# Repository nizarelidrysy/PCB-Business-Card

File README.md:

# Nizar's PCB Business Card

This repository contains an open hardware business card running open source
software.

## Getting started

### Hardware

Using KiCad, add Silkscreen details such as your name. E.g. I added my contact
details and word cloud of my skills on the back of the PCB. Using the PCB Way
fabrication plugin of KiCAD, you can export the production files to directly
order the PCBs.

Note that when using vanilla PCB options (1.6 mm PCB thickness, HASL surface
finish) the USB connector will be a tad too thin to perfectly make contact with
a USB socket. Ideally you would use 2.0 mm PCB thickness and ENIG surface
finish, but that would be so expensive that it defeats the purpose of a
business card. Instead, you can just add a bit of solder on the USB contacts to
increase the thickness.

### Software

A simple "hello world" demo is given in
`software/RIOT-based-apps/apps/hello-world` that you can flash using e.g. a
J-Link EDU Mini programmer. Rather than using a cable, just plug the pins of
the J-Link EDU Mini programmer from the underside through the holes and rotate
the programmer until the pins and holes have contact. In addition, you need to
power the board (ideally via a USB-A extension cord).

With the programmer connected and the board powered, simply run:

    make flash

The "default" application will be `software/RIOT-based-apps/apps/games`, as
this contains a game launcher that allows running all currently added games.

Refer to the [RIOT documentation](https://doc.riot-os.org/) for more details on
the software.

---

<div align="center">
  <p>Engineered with dedication by Nizar EL IDRYSY ❤️</p>
</div>

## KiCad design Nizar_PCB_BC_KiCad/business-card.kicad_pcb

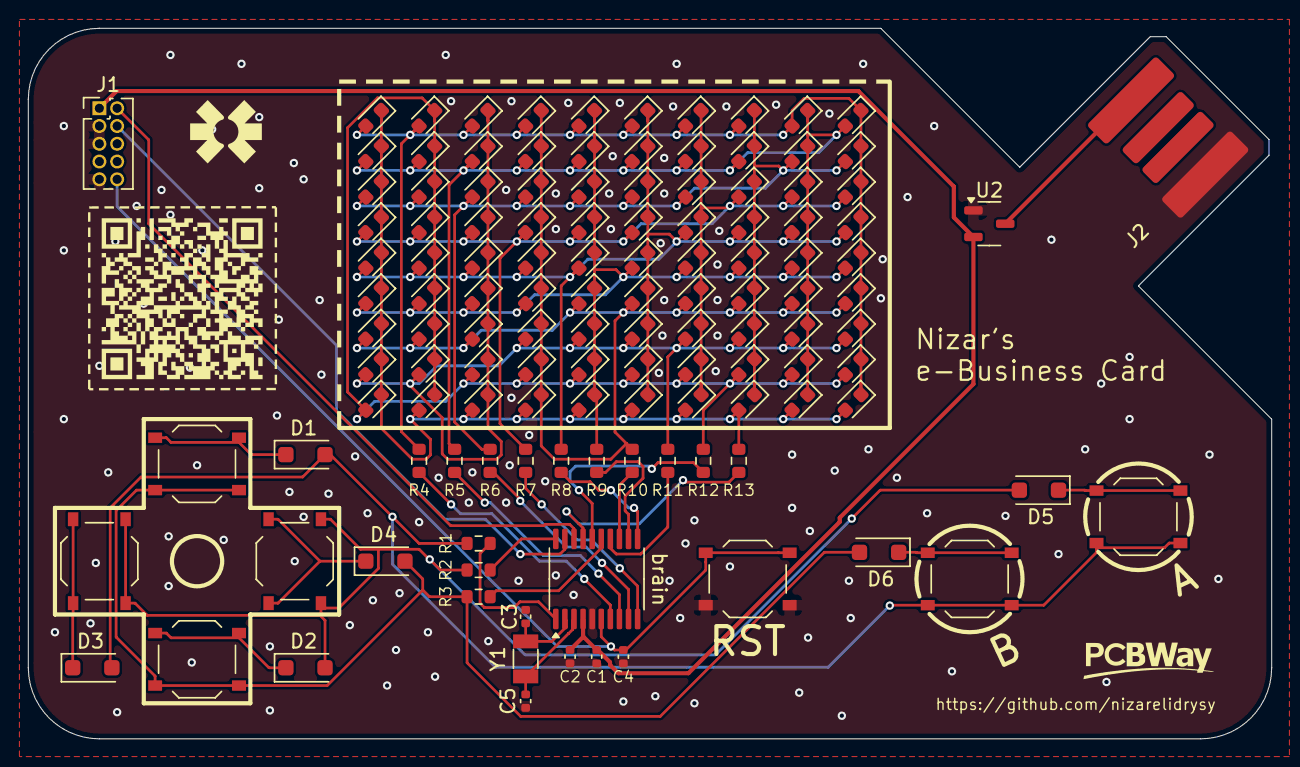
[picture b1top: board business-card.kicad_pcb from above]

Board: 2 copper layers, 88.9 x 50.8 mm, 126 parts (0 on the bottom side), 40 nets.

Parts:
C1, C4: 100 nF; C_0402_1005Metric
C2: 4.7 uF; C_0402_1005Metric
C3, C5: 10 pF; C_0402_1005Metric
D1, D2, D3, D4, D5, D6: D; D_SOD-123F
D7, D8, D9, D10, D11, D12, D13, D14, D15, D16, D17, D18, D19, D20, D21, D22, D23, D24, D25, D26, D27, D28, D29, D30, D31, D32, D33, D34, D35, D36, D37, D38, D39, D40, D41, D42, D43, D44, D45, D46, D47, D48, D49, D50, D51, D52, D53, D54, D55, D56, D57, D58, D59, D60, D61, D62, D63, D64, D65, D66, D67, D68, D69, D70, D71, D72, D73, D74, D75, D76, D77, D78, D79, D80, D81, D82, D83, D84, D85, D86, D87, D88, D89, D90, D91, D92, D93, D94, D95, D96: LED; LED_0603_1608Metric
J1: SWD; PinHeader_2x05_P1.27mm_Vertical
J2: USB_A_PCB_Edge_receptacle
R1, R2, R3, R4, R5, R6, R7, R8, R9, R10, R11, R12, R13: 75R; R_0603_1608Metric
SW1: BTN_UP; SW_Push_1P1T_XKB_TS-1187A
SW2: BTN_DOWN; SW_Push_1P1T_XKB_TS-1187A
SW3: BTN_LEFT; SW_Push_1P1T_XKB_TS-1187A
SW4: BTN_RIGHT; SW_Push_1P1T_XKB_TS-1187A
SW5: RST; SW_Push_1P1T_XKB_TS-1187A
SW6: BTN_A; SW_Push_1P1T_XKB_TS-1187A
SW7: BTN_B; SW_Push_1P1T_XKB_TS-1187A
U2: XC6206P332MR-G; SOT-23-3
Y1: 32.678 kHz; Crystal_SMD_3215-2Pin_3.2x1.5mm
brain: STM32G030F6Px; TSSOP-20_4.4x6.5mm_P0.65mm

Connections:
+5V: J2.1 (VBUS), U2.3 (VI)
/BM1: R1.1, brain.1 (PB7/PB8)
/BM2: R2.1, brain.20 (PB3/PB4/PB5/PB6)
/BM3: R3.1, brain.15 (PB0/PB1/PB2/PA8)
/NRST: C4.1, J1.10 (~RESET), SW5.1, brain.6 (NRST)
/OSC32_N: C3.1, Y1.1, brain.2 (PC14/PB9)
/OSC32_P: C5.1, Y1.2, brain.3 (PC15)
/PA0: R4.1, brain.7 (PA0)
/PA1: R5.1, brain.8 (PA1)
/PA2: R6.1, brain.9 (PA2)
/PA3: R7.1, brain.10 (PA3)
/PA4: R8.1, brain.11 (PA4)
/PA5: R9.1, brain.12 (PA5)
/PA6: R10.1, brain.13 (PA6)
/PA7: R11.1, brain.14 (PA7)
/PA9: R12.1, brain.16 (PA11/PA9)
/PA10: R13.1, brain.17 (PA12/PA10)
/SWCLK: J1.4 (SWCLK/TCK), brain.19 (PA14/PA15)
/SWDIO: J1.2 (SWDIO/TMS), brain.18 (PA13)
GND: C1.2, C2.2, C3.2, C4.2, C5.2, J1.3 (GND), J1.5 (GND), J1.9 (GNDDetect), J2.4 (GND), SW5.2, U2.1 (GND), brain.5 (VSS)
unnamed: D1.2 (A), D3.2 (A), R1.2, SW6.2, SW7.2
unnamed: D1.1 (K), SW1.1
unnamed: D2.2 (A), D5.2 (A), R2.2, SW3.2, SW4.2
unnamed: D2.1 (K), SW2.1
unnamed: D3.1 (K), SW3.1
unnamed: D4.2 (A), D6.2 (A), R3.2, SW1.2, SW2.2
unnamed: D4.1 (K), SW4.1
unnamed: D5.1 (K), SW6.1
unnamed: D6.1 (K), SW7.1
unnamed: D10.2 (A), D19.2 (A), D28.2 (A), D37.2 (A), D46.2 (A), D55.2 (A), D61.1 (K), D62.1 (K), D63.1 (K), D64.1 (K), D65.1 (K), D66.1 (K), D67.1 (K), D68.1 (K), D69.1 (K), D72.2 (A), D81.2 (A), D90.2 (A), R7.2
unnamed: D7.1 (K), D8.1 (K), D9.1 (K), D10.1 (K), D11.1 (K), D12.1 (K), D13.1 (K), D14.1 (K), D15.1 (K), D24.2 (A), D33.2 (A), D42.2 (A), D51.2 (A), D60.2 (A), D69.2 (A), D78.2 (A), D87.2 (A), D96.2 (A), R13.2
unnamed: D11.2 (A), D20.2 (A), D29.2 (A), D38.2 (A), D47.2 (A), D52.1 (K), D53.1 (K), D54.1 (K), D55.1 (K), D56.1 (K), D57.1 (K), D58.1 (K), D59.1 (K), D60.1 (K), D64.2 (A), D73.2 (A), D82.2 (A), D91.2 (A), R8.2
unnamed: D12.2 (A), D21.2 (A), D30.2 (A), D39.2 (A), D43.1 (K), D44.1 (K), D45.1 (K), D46.1 (K), D47.1 (K), D48.1 (K), D49.1 (K), D50.1 (K), D51.1 (K), D56.2 (A), D65.2 (A), D74.2 (A), D83.2 (A), D92.2 (A), R9.2
unnamed: D13.2 (A), D22.2 (A), D31.2 (A), D34.1 (K), D35.1 (K), D36.1 (K), D37.1 (K), D38.1 (K), D39.1 (K), D40.1 (K), D41.1 (K), D42.1 (K), D48.2 (A), D57.2 (A), D66.2 (A), D75.2 (A), D84.2 (A), D93.2 (A), R10.2
unnamed: D14.2 (A), D23.2 (A), D25.1 (K), D26.1 (K), D27.1 (K), D28.1 (K), D29.1 (K), D30.1 (K), D31.1 (K), D32.1 (K), D33.1 (K), D40.2 (A), D49.2 (A), D58.2 (A), D67.2 (A), D76.2 (A), D85.2 (A), D94.2 (A), R11.2
unnamed: D15.2 (A), D16.1 (K), D17.1 (K), D18.1 (K), D19.1 (K), D20.1 (K), D21.1 (K), D22.1 (K), D23.1 (K), D24.1 (K), D32.2 (A), D41.2 (A), D50.2 (A), D59.2 (A), D68.2 (A), D77.2 (A), D86.2 (A), D95.2 (A), R12.2
unnamed: D7.2 (A), D16.2 (A), D25.2 (A), D34.2 (A), D43.2 (A), D52.2 (A), D61.2 (A), D70.2 (A), D79.2 (A), D88.1 (K), D89.1 (K), D90.1 (K), D91.1 (K), D92.1 (K), D93.1 (K), D94.1 (K), D95.1 (K), D96.1 (K), R4.2
unnamed: D8.2 (A), D17.2 (A), D26.2 (A), D35.2 (A), D44.2 (A), D53.2 (A), D62.2 (A), D71.2 (A), D79.1 (K), D80.1 (K), D81.1 (K), D82.1 (K), D83.1 (K), D84.1 (K), D85.1 (K), D86.1 (K), D87.1 (K), D88.2 (A), R5.2
unnamed: D9.2 (A), D18.2 (A), D27.2 (A), D36.2 (A), D45.2 (A), D54.2 (A), D63.2 (A), D70.1 (K), D71.1 (K), D72.1 (K), D73.1 (K), D74.1 (K), D75.1 (K), D76.1 (K), D77.1 (K), D78.1 (K), D80.2 (A), D89.2 (A), R6.2
VDD: C1.1, C2.1, J1.1 (VTref), U2.2 (VO), brain.4 (VDD)
